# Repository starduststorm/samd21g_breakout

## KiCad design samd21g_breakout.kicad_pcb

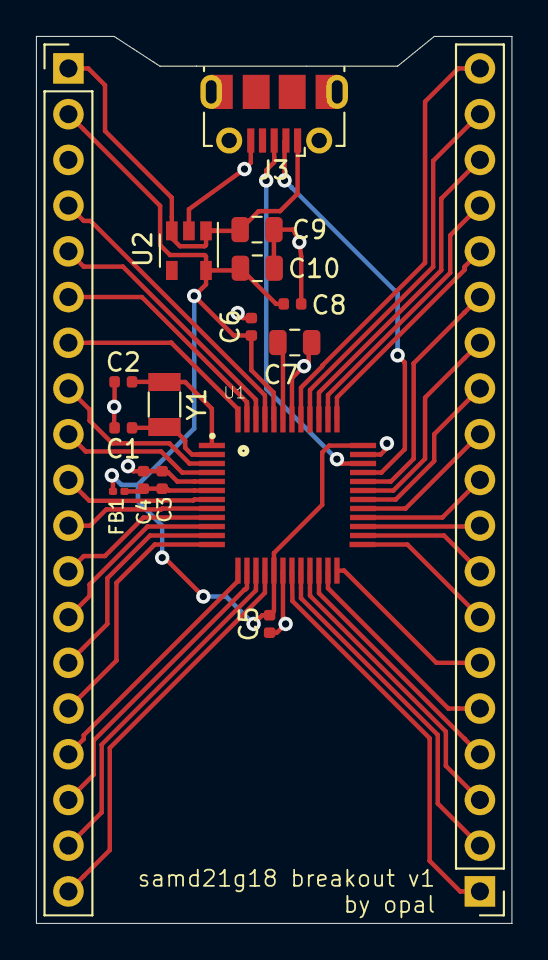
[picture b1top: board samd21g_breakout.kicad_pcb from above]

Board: 2 copper layers, 26.4 x 49.3 mm, 17 parts (0 on the bottom side), 44 nets.

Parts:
C1, C2: 15pF; C_0402_1005Metric
C3, C5, C6: 100nF; C_0402_1005Metric
C4, C8: 10µF; C_0402_1005Metric
C7, C9, C10: 1µF; C_0805_2012Metric
FB1: 220Ω @ 100MHz; L_0201_0603Metric
J1, J2: Conn_01x19; PinHeader_1x19_P2.54mm_Vertical
J3: USB_B_Micro; USB_Micro-B_Molex-105017-0001
U1: ATSAMD21G18A-AU; QFP50P900X900X120-48N
U2: MIC5504-3.3YM5; SOT-23-5
Y1: 32768Hz; Crystal_SMD_3215-2Pin_3.2x1.5mm

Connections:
+3V3: C5.2, C6.1, C8.1, C10.1, FB1.1, J1.2, U1.17, U1.36, U1.44, U2.5
GND: C1.2, C2.2, C3.2, C4.1, C5.1, C6.2, C7.2, C8.2, C9.2, C10.2, J1.3, J3.5, U1.5, U1.18, U1.35, U1.42, U2.2
unnamed: C1.1, U1.2, Y1.2
unnamed: C2.1, U1.1, Y1.1
unnamed: C3.1, C4.2, FB1.2, U1.6
unnamed: C7.1, U1.43
PA02: J1.8, U1.3
PA03: J1.9, U1.4
PA04: J1.12, U1.9
PA05: J1.13, U1.10
PA06: J1.14, U1.11
PA07: J1.15, U1.12
PA08: J1.16, U1.13
PA09: J1.17, U1.14
PA10: J1.18, U1.15
PA11: J1.19, U1.16
PA12: J2.3, U1.21
PA13: J2.4, U1.22
PA14: J2.5, U1.23
PA15: J2.6, U1.24
PA16: J2.7, U1.25
PA17: J2.8, U1.26
PA18: J2.9, U1.27
PA19: J2.10, U1.28
PA20: J2.11, U1.29
PA21: J2.12, U1.30
PA22: J2.13, U1.31
PA23: J2.14, U1.32
PA27: J2.17, U1.39
PA28: J2.19, U1.41
PA30: J1.4, U1.45
PA31: J1.5, U1.46
PB02: J1.6, U1.47
PB03: J1.7, U1.48
PB08: J1.10, U1.7
PB09: J1.11, U1.8
PB10: J2.1, U1.19
PB11: J2.2, U1.20
PB22: J2.15, U1.37
PB23: J2.16, U1.38
RESET: J2.18, U1.40
USB_D+: J3.3, U1.34
USB_D-: J3.2, U1.33
VBUS: C9.1, J1.1, J3.1, U2.1, U2.3

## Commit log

2020-05-12 initial commit, v1 sent to printer
2020-10-20 fixed some absolute paths; fixed broken symbol reference and re-saved
2022-07-19 update to kicad 6 format
